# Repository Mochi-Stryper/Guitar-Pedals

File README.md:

# Guitar-Pedals
**Guitar Effects**

SMD adapted guitar effects with a keen eye on condensing parameters and grossly placed LDRs.
Not a second has been wasted considering ergonomics or intellectual property.

_Currently Unverified!_

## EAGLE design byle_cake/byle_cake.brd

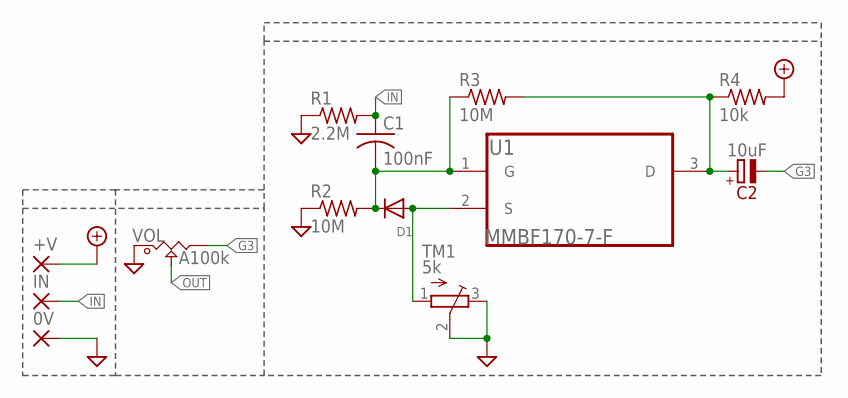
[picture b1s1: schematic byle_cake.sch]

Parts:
0V: SMD2; SMD1,27-2,54
+V: SMD2; SMD1,27-2,54
C1: 100nF; C0603
C2: 10uF; PAN_B
D1: DIODESOD-123; SOD-123
IN: SMD2; SMD1,27-2,54
R1: 2.2M; R0603
R2, R3: 10M; R0603
R4: 10k; R0603
TM1: 5k; TC33X
U1: MMBF170-7-F; SOT103P240X110-3N
VOL: A100k; POT_9MM_SMD

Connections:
+9V: +V.1, R4.2
G3: C2.2- (-), VOL.3
GND: 0V.1, R1.1, R2.1, TM1.2 (S), TM1.3 (E), VOL.1
IN: C1.1, IN.1, R1.2
unnamed: C1.2, D1.C, R2.2, R3.1, U1.1 (G)
unnamed: D1.A, TM1.1 (A), U1.2 (S)
unnamed: C2.1+ (+), R3.2, R4.1, U1.3 (D)
OUT: VOL.2

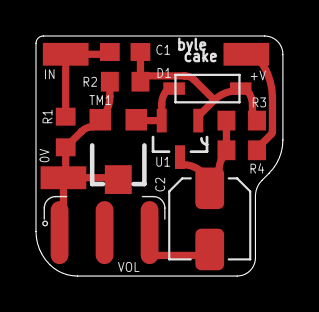
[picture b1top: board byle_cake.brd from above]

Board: 2 copper layers, 13.7 x 13.3 mm, 13 parts (0 on the bottom side), 7 nets.

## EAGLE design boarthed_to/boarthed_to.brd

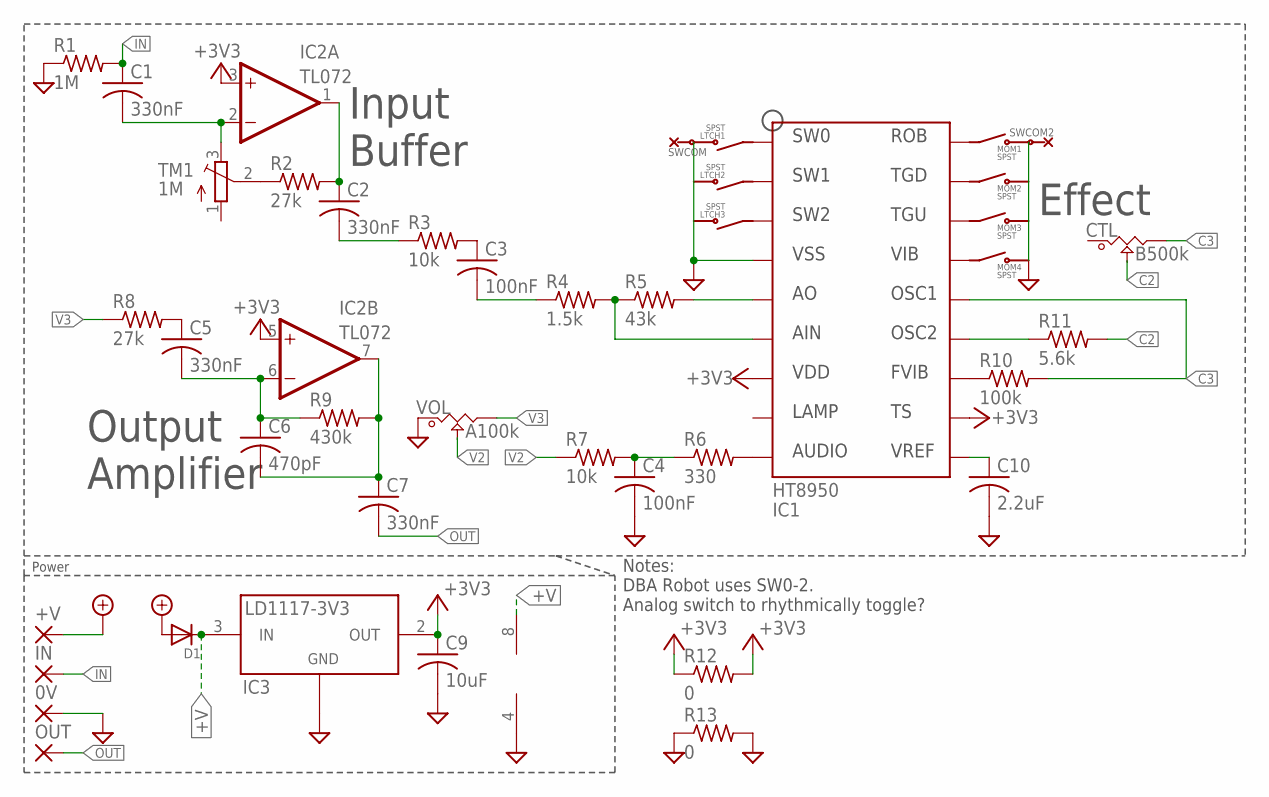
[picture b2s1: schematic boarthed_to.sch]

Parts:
0V: SMD2; SMD1,27-2,54
+V: SMD2; SMD1,27-2,54
C1, C2, C5, C7: 330nF; C0603
C3, C4: 100nF; C0603
C6: 470pF; C0603
C9: 10uF; C1206
C10: 2.2uF; C0603
CTL: B500k; POT_9MM_SMD
D1: DIODESOD-123; SOD-123
IC2: TL072; TSSOP-8
IC3: LD1117-3V3; SOT-223
IN: SMD2; SMD1,27-2,54
LTCH1, LTCH2, LTCH3: SPST_1PAD; 1PAD
MOM1, MOM2, MOM3, MOM4: SPST_1PAD; 1PAD
OUT: SMD2; SMD1,27-2,54
R1: 1M; R0603
R2, R8: 27k; R0603
R3, R7: 10k; R0603
R4: 1.5k; R0603
R5: 43k; R0603
R6: 330; R0603
R9: 430k; R0603
R10: 100k; R0603
R11: 5.6k; R0603
R12, R13: 0; R0402
SWCOM, SWCOM2: COM_SMD; 1PAD
TM1: 1M; TC33X
U$4: HT8950; PDIP-18
VOL: A100k; POT_9MM_SMD

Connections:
+3V3: C9.1, IC2.3 (+IN), IC2.5 (+IN), IC3.2 (OUT), IC3.4, R12.1, R12.2, U$4.7 (VDD), U$4.11 (TS)
+9V: +V.1, D1.A
+V: D1.C, IC2.8 (V+), IC3.3 (IN)
C2: CTL.2, R11.2
C3: CTL.3, R10.2, U$4.14 (OSC1)
GND: 0V.1, C4.2, C9.2, C10.2, IC2.4 (V-), IC3.1 (ADJ/GND), R1.1, R13.1, R13.2, SWCOM.1, SWCOM2.1, U$4.4 (VSS), VOL.1
IN: C1.1, IN.1, R1.2
unnamed: LTCH1.1, U$4.1 (SW0)
unnamed: LTCH2.1, U$4.2 (SW1)
unnamed: LTCH3.1, U$4.3 (SW2)
unnamed: MOM1.1, U$4.18 (ROB)
unnamed: MOM2.1, U$4.17 (TGD)
unnamed: MOM3.1, U$4.16 (TGU)
unnamed: MOM4.1, U$4.15 (VIB)
unnamed: C10.1, U$4.10 (VREF)
unnamed: C1.2, IC2.2 (-IN), TM1.3 (E)
unnamed: R2.1, TM1.2 (S)
unnamed: C2.1, IC2.1 (OUT), R2.2
unnamed: C2.2, R3.1
unnamed: C3.1, R3.2
unnamed: C3.2, R4.1
unnamed: R4.2, R5.1, U$4.6 (AIN)
unnamed: R5.2, U$4.5 (AO)
unnamed: R6.2, U$4.9 (AUDIO)
unnamed: C4.1, R6.1, R7.2
unnamed: C5.1, R8.2
unnamed: C5.2, C6.1, IC2.6 (-IN), R9.1
unnamed: C6.2, C7.1, IC2.7 (OUT), R9.2
unnamed: R10.1, U$4.12 (FVIB)
unnamed: R11.1, U$4.13 (OSC2)
OUT: C7.2, OUT.1
V2: R7.1, VOL.2
V3: R8.1, VOL.3

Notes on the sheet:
Power
Input Buffer
Effect
Output Amplifier
Notes: DBA Robot uses SW0-2.
Analog switch to rhythmically toggle?

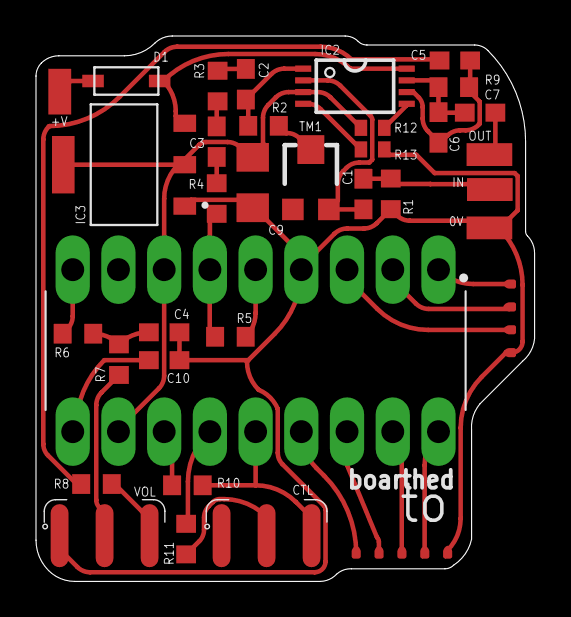
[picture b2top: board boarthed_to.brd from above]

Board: 2 copper layers, 27.7 x 30.3 mm, 42 parts (0 on the bottom side), 33 nets.

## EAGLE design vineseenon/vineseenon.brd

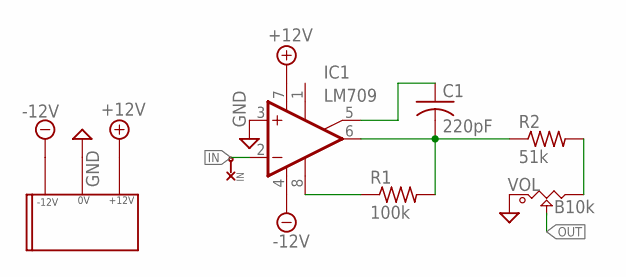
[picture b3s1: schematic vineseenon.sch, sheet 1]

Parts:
C1: 220pF; C0603
IC1: LM709; DIL08
IN: PAD; 1PAD_B
R1: 100k; R0603
R2: 51k; R0603
U$1: EURO_POW_CEH
VOL: B10k; POT_9MM_SMD

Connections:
+12V: IC1.7 (V+), U$1.+12V
-12V: IC1.4 (V-), U$1.-12V
GND: IC1.3 (+IN), U$1.GND, VOL.1
IN: IC1.2 (-IN), IN.1
unnamed: IC1.8 (OPT), R1.1
unnamed: C1.2, IC1.6 (OUT), R1.2, R2.1
unnamed: C1.1, IC1.5 (ON2)
unnamed: R2.2, VOL.3
OUT: VOL.2

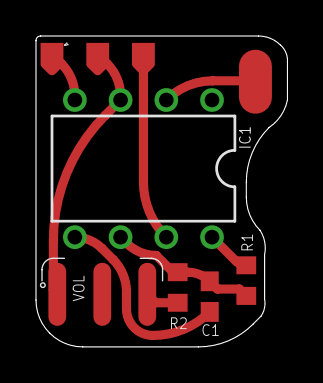
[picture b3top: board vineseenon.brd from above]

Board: 2 copper layers, 14.0 x 17.3 mm, 7 parts (0 on the bottom side), 8 nets.

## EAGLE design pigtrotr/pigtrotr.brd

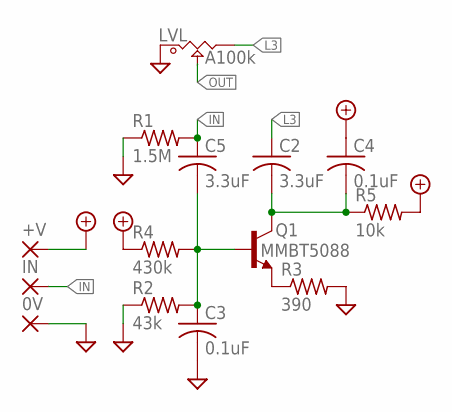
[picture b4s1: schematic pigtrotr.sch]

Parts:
0V: SMD2; SMD1,27-2,54
+V: SMD2; SMD1,27-2,54
C2: 3.3uF; C0805
C3, C4: 0.1uF; C0603
C5: 3.3uF; C1206
IN: SMD2; SMD1,27-2,54
LVL: A100k; POT_9MM_SMD
Q1: MMBT5088; SOT23-BEC
R1: 1.5M; R0603
R2: 43k; R0603
R3: 390; R0603
R4: 430k; R0603
R5: 10k; R0603

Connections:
+9V: +V.1, C4.1, R4.1, R5.2
GND: 0V.1, C3.2, LVL.1, R1.1, R2.1, R3.2
IN: C5.1, IN.1, R1.2
L3: C2.1, LVL.3
unnamed: Q1.E, R3.1
unnamed: C3.1, C5.2, Q1.B, R2.2, R4.2
unnamed: C2.2, C4.2, Q1.C, R5.1
OUT: LVL.2

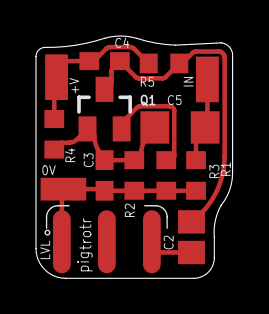
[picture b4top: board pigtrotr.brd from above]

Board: 2 copper layers, 10.9 x 13.5 mm, 14 parts (0 on the bottom side), 7 nets.

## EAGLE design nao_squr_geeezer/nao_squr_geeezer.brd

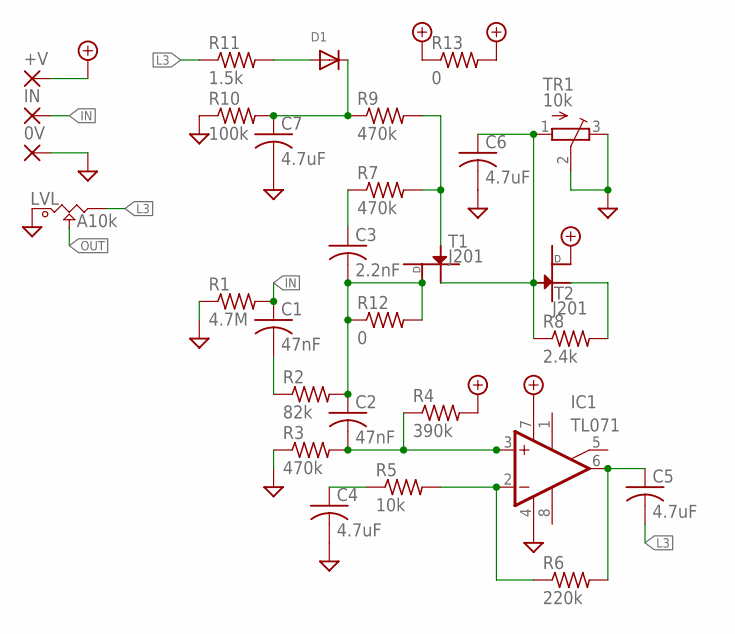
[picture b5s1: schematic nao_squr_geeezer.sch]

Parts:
0V: SMD2; SMD1,27-2,54
+V: SMD2; SMD1,27-2,54
C1, C2: 47nF; C0603
C3: 2.2nF; C0603
C4: 4.7uF; C1206
C5, C6, C7: 4.7uF; C0805
D1: DIODESOD-123; SOD-123
IC1: TL071; SO08
IN: SMD2; SMD1,27-2,54
LVL: A10k; POT_9MM_SMD
R1: 4.7M; R0603
R2: 82k; R0603
R3, R7, R9: 470k; R0603
R4: 390k; R0603
R5: 10k; R0603
R6: 220k; R0603
R8: 2.4k; R0603
R10: 100k; R0603
R11: 1.5k; R0603
R12: 0; R0402
R13: 0; R0603
T1, T2: J201; MMBFJ201
TR1: 10k; TC33X

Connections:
+9V: +V.1, IC1.7 (V+), R4.2, R13.1, R13.2, T2.D
GND: 0V.1, C4.2, C6.2, C7.2, IC1.4 (V-), LVL.1, R1.1, R3.1, R10.1, TR1.2 (S), TR1.3 (E)
IN: C1.1, IN.1, R1.2
L3: C5.2, LVL.3, R11.1
unnamed: C1.2, R2.1
unnamed: C2.1, C3.2, R2.2, R12.1, R12.2, T1.D
unnamed: C2.2, IC1.3 (+IN), R3.2, R4.1
unnamed: IC1.2 (-IN), R5.2, R6.1
unnamed: C4.1, R5.1
unnamed: C5.1, IC1.6 (OUT), R6.2
unnamed: C3.1, R7.1
unnamed: R7.2, R9.2, T1.G
unnamed: C6.1, R8.1, T1.S, T2.G, TR1.1 (A)
unnamed: R8.2, T2.S
unnamed: C7.1, D1.C, R9.1, R10.2
unnamed: D1.A, R11.2
OUT: LVL.2

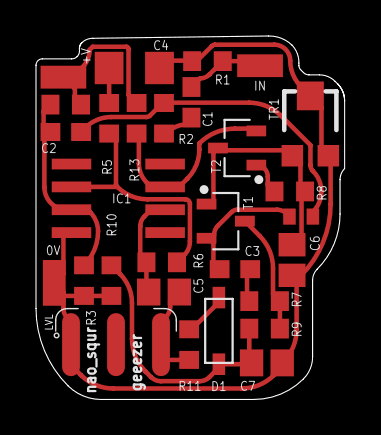
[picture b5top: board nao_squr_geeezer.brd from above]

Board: 2 copper layers, 17.1 x 20.2 mm, 29 parts (0 on the bottom side), 16 nets.

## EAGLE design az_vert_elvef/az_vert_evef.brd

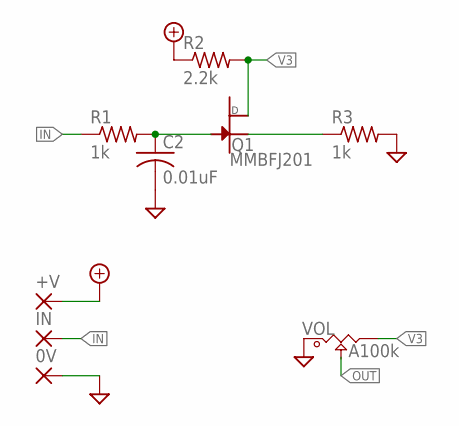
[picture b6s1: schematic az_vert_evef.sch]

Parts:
0V: SMD2; SMD1,27-2,54
+V: SMD2; SMD1,27-2,54
C2: 0.01uF; C0603
IN: SMD2; SMD1,27-2,54
Q1: MMBFJ201
R1, R3: 1k; R0603
R2: 2.2k; R0603
VOL: A100k; POT_9MM_SMD

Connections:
+9V: +V.1, R2.1
GND: 0V.1, C2.2, R3.2, VOL.1
IN: IN.1, R1.1
unnamed: C2.1, Q1.G, R1.2
unnamed: Q1.S, R3.1
OUT: VOL.2
V3: Q1.D, R2.2, VOL.3

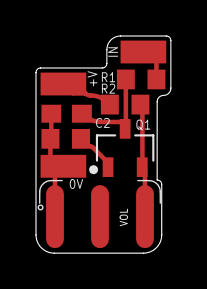
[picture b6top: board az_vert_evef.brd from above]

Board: 2 copper layers, 7.5 x 12.1 mm, 9 parts (0 on the bottom side), 6 nets.

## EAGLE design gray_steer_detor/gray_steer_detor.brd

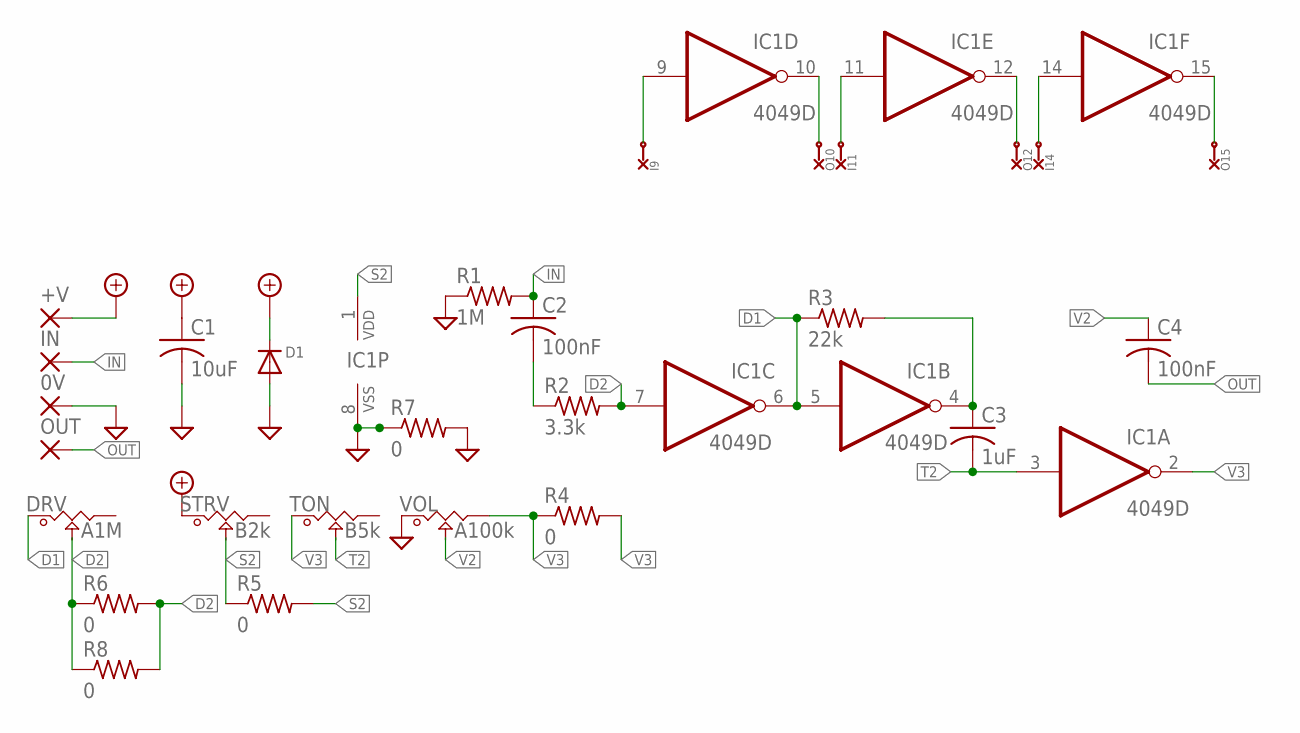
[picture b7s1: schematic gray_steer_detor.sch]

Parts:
0V: SMD2; SMD1,27-2,54
+V: SMD2; SMD1,27-2,54
C1: 10uF; C1206
C2, C4: 100nF; C0603
C3: 1uF; C0603
D1: DIODESOD-123; SOD-123
DRV: A1M; POT_9MM_SMD
I9, I11, I14: COM_SMD; 1PAD
IC1: 4049D; SO16
IN: SMD2; SMD1,27-2,54
O10, O12, O15: COM_SMD; 1PAD
OUT: SMD2; SMD1,27-2,54
R1: 1M; R0603
R2: 3.3k; R0603
R3: 22k; R0603
R4, R5, R6, R7, R8: 0; R0402
STRV: B2k; POT_9MM_SMD
TON: B5k; POT_9MM_SMD
VOL: A100k; POT_9MM_SMD

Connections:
+9V: +V.1, C1.1, D1.C, STRV.1
D1: DRV.1, IC1.5 (I), IC1.6 (O), R3.1
D2: DRV.2, IC1.7 (I), R2.2, R6.1, R6.2, R8.1, R8.2
GND: 0V.1, C1.2, D1.A, IC1.8 (VSS), R1.1, R7.1, R7.2, VOL.1
I9: I9.1, IC1.9 (I)
I11: I11.1, IC1.11 (I)
I14: I14.1, IC1.14 (I)
IN: C2.1, IN.1, R1.2
unnamed: C2.2, R2.1
O4: C3.1, IC1.4 (O), R3.2
O10: IC1.10 (O), O10.1
O12: IC1.12 (O), O12.1
O15: IC1.15 (O), O15.1
OUT: C4.2, OUT.1
S2: IC1.1 (VDD), R5.1, R5.2, STRV.2
T2: C3.2, IC1.3 (I), TON.2
V2: C4.1, VOL.2
V3: IC1.2 (O), R4.1, R4.2, TON.1, VOL.3

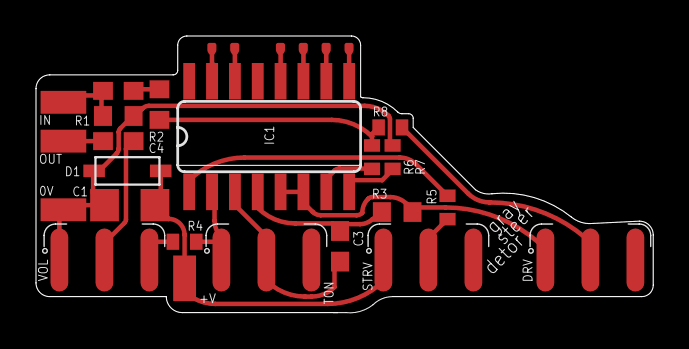
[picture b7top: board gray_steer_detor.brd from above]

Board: 2 copper layers, 34.3 x 15.4 mm, 28 parts (0 on the bottom side), 18 nets.

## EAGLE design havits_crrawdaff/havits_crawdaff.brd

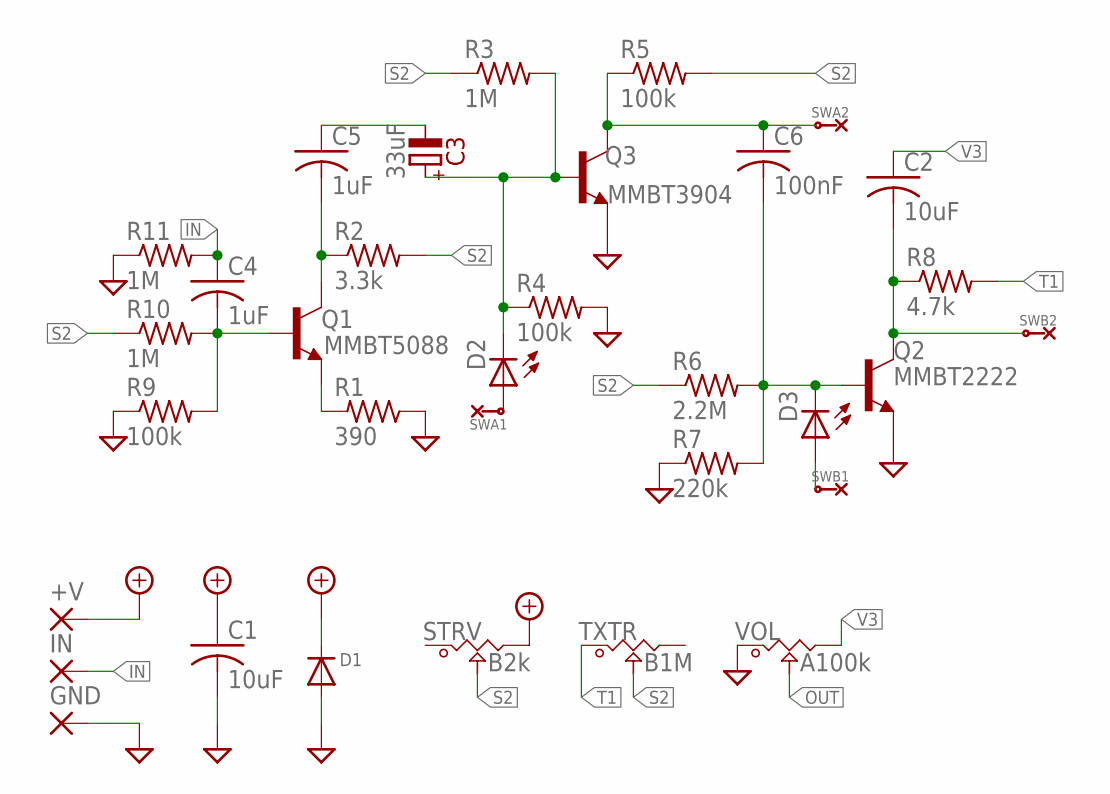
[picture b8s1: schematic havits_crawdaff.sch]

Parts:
+V: SMD2; SMD1,27-2,54
C1, C2: 10uF; C1206
C3: 33uF; PAN_B
C4, C5: 1uF; C0603
C6: 100nF; C0603
D1: DIODESOD-123; SOD-123
D2, D3: LEDCHIPLED_0603; CHIPLED_0603
GND: SMD2; SMD1,27-2,54
IN: SMD2; SMD1,27-2,54
Q1: MMBT5088; SOT23-BEC
Q2: MMBT2222; SOT23-BEC
Q3: MMBT3904; SOT23-3
R1: 390; R0603
R2: 3.3k; R0603
R3, R10, R11: 1M; R0603
R4, R5, R9: 100k; R0603
R6: 2.2M; R0603
R7: 220k; R0603
R8: 4.7k; R0603
STRV: B2k; POT_9MM_SMD
SWA1, SWA2: COM_SMD; 1PAD
SWB1, SWB2: COM_SMD; 1PAD
TXTR: B1M; POT_9MM_SMD
VOL: A100k; POT_9MM_SMD

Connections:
+9V: +V.1, C1.1, D1.C, STRV.3
GND: C1.2, D1.A, GND.1, Q2.E, Q3.2 (E), R1.1, R4.2, R7.1, R9.1, R11.1, VOL.1
IN: C4.1, IN.1, R11.2
unnamed: D3.A, SWB1.1
unnamed: C3.2- (-), C5.1
unnamed: D2.A, SWA1.1
OUT: VOL.2
Q1_B: C4.2, Q1.B, R9.2, R10.2
Q1_C: C5.2, Q1.C, R2.1
Q1_E: Q1.E, R1.2
Q2_B: C6.2, D3.C, Q2.B, R6.2, R7.2
Q2_C: C2.2, Q2.C, R8.1, SWB2.1
Q3_B: C3.1+ (+), D2.C, Q3.1 (B), R3.2, R4.1
Q3_C: C6.1, Q3.3 (C), R5.1, SWA2.1
S2: R2.2, R3.1, R5.2, R6.1, R10.1, STRV.2, TXTR.2
T1: R8.2, TXTR.1
V3: C2.1, VOL.3

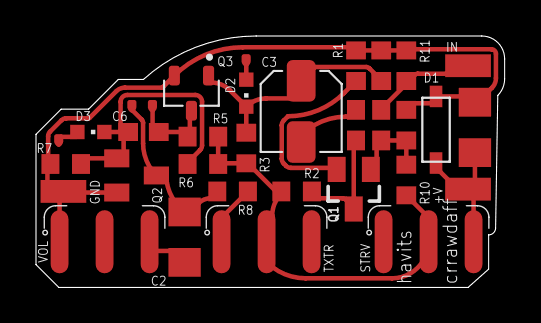
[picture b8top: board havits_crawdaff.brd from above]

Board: 2 copper layers, 26.0 x 14.0 mm, 33 parts (0 on the bottom side), 16 nets.

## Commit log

2020-09-29 Guitar Pedals
    SMD adapted guitar effects with a keen eye on condensing parameters and grossly placed LDRs. Not a second has been wasted considering ergonomics or intellectual property. Sorry!
2020-09-29 Removed redundancies
2020-09-30 Create ReadMe
    ~Incomplete~
    Fuzz Factory
    Voltage Starved Fuzz Face
    PlayStation Joystick
    Incorrect Starve Parameter Voltage
2020-10-15 Added brd sch
    Added brd sch
2020-10-16 Added JFET Send/Return
    Added JFET Send/Return
2020-10-16 Added Moof Janibore
    Added Moof Janibore
2020-10-17 Added Pawmeat_Ton
    Added Pawmeat_Ton
2020-10-17 Added Moses_Ft._Creamer
    Added Moses_Ft._Creamer
2020-10-18 Added uRusset_Meeper_Barc
    Added uRusset_Meeper_Barc
2020-10-19 Added EHX Boosts
    Added Blo_Pen & shoo_gtfo
2020-10-19 Added Vest_Belter_Borox
    Added Vest_Belter_Borox
2020-10-19 Edited Description
    Edited Description
2020-10-19 Added mush_indi_gnat
    Added mush_indi_gnat
2020-10-20 Added re:bent_hum_singe
    Added re:bent_hum_singe
2020-10-20 Create DESCRIPTION
    Create DESCRIPTION
2020-10-20 Added looter_round_molocs
    Added looter_round_molocs
2020-10-21 Uploaded rifting_bronx_eden
    Uploaded rifting_bronx_eden
2020-10-21 Added LT1054_Daughterboard
    Added LT1054_Daughterboard
2020-10-22 Added aHam_just_captm
    Added aHam_just_captm
2020-10-22 create DESCRIPTION.txt
    create DESCRIPTION.txt
2020-10-22 Delete DESCRIPTION.txt
    Delete DESCRIPTION.txt
2020-10-22 Create README
    Create README
2020-10-22 Added README
    Added README
2020-10-22 Added dermabragun_mentor_reno
    Added dermabragun_mentor_reno
2020-10-22 Added 3PDT_2FX
    Added 3PDT_2FX
2020-10-22 Added ode_qt_ex
    Added ode_qt_ex
2020-10-23 Added bee_duel_played
    Added bee_duel_played
2020-10-23 Added iBuff_gimp
    Added iBuff_gimp
2020-10-24 Added higs_bc_eee
    Added higs_bc_eee
2020-10-26 added thit_draw103
    added thit_draw103
2020-10-26 Added nor_ppalette
    Added nor_ppalette
2020-10-30 Added rita_milton_civ
    Added rita_milton_civ
2020-11-01 Added axe_tomb
    Added axe_tomb
2020-11-01 Added streamr_math_nap
    Added streamr_math_nap
2020-11-02 compashin_izzonu_fine
    compashin_izzonu_fine
2020-11-03 tee_dweebo
    tee_dweebo
2020-11-04 as_wounds
    as_wounds
2020-11-05 soar_demise
    soar_demise
2020-11-06 moe_tuned_lens
    moe_tuned_lens
2020-11-07 a_civil_hero_vermin_orderv
    a_civil_hero_vermin_orderv
2022-04-03 Added ublisterred_vow
    Added ublisterred_vow, an overdrive stompbox.
2022-04-04 Added succh_punker
    Added succh_punker
2022-04-09 Added plumxsodrodd
    Added plumxsodrodd
2022-04-09 Added scary_rubber
    Added scary_rubber
2022-04-09 Added ha_notchecker
    Added ha_notchecker
2022-04-10 Added round_paws_2
    Added round_paws_2
2022-04-14 Added havits_crrawdaff
    Added havits_crrawdaff
2022-04-14 Added gray_steer_detor
    Added gray_steer_detor
2022-04-14 Added az_vert_elvef
    Added az_vert_elvef
2022-04-30 Added nao_squr_geeezer
    Added nao_squr_geeezer
2022-04-30 Added pigtrotr
    Added pigtrotr
2022-05-02 Added 4Show_CE
    Added 4Show_CE
2022-05-03 Added vineseenon
    Added vineseenon
2022-05-03 Added boarthed_to, merged designs
    Added boarthed_to, merged designs
2022-05-07 Added byle_cake
    Added byle_cake
